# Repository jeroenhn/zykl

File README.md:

# ReZyklus Project

## A clone of the Zyklus MPS-1

The **ReZyklus Project** is an open-source effort to recreate the original **Zyklus MPS-1**.

This repository contains everything required to build your own Zyklus MPS-1 clone, aptly named 'ReZyklus', including hardware design files, panel layouts, and supporting documentation.

See my blog for some more info on the project:
https://www.zyklus-mps.com

There is a Discord server you can join specifically for this project:
https://discord.gg/zFuuCRRDz4

This is also the place where we think and talk about a succesor, the V2 which is mainly carried by David Perbal and will be a system based on the Teensy platform most likely. 

So what is the Zyklus MPS-1? 
A Midi Performance System. It's more than just a sequencer, it's kinda like an 80's version of a launchpad. 
There's really no better way to understand than to have one of the original developers show it to you, so check out Pete Kellocks video demo's of the Zyklus:
https://zyklus-mps.com/videos

Shout out to the team:

Paul McMurray (Technical genius who did most of the actual cloning work)

Marcel Donné (Tester/builder who build one of the first clones)

David Perbal (Another tester/builder who build two of 'm and is carrying the V2 project for the succesor of the ReZyklus - a Teensy based modern implementation)

Panu Talus (Zyklus enthausiast who for years has accumulated all sorts of historical information on the various units. Owner of an original)

And I'm Jeroen (Vangelis gear nut, founder of this project, also owns 2 originals and is restoring Vangelis orignal 'Direct' system).

---

## What’s in this repository

- **Bill of Materials (BOM)**  
  Detailed BOM spreadsheets provide a complete shopping list for the build.

- **PCB & Panel Design Files**  
  All PCB designs and front-panel files are provided.  
  The boards and panels were manufactured using **JLCPCB**, noting that their minimum order quantity is typically **5 units per board or panel**.

- **Case Parts**  
  Some enclosure components are **3D-printed**.  
  The required STL files are included in the repository.

- **Aluminium Dials**  
  Custom aluminium dials were also produced through **JLCPCB**, a working stepfile is included. The Case Parts also contain a file for a 3d printed version. 
  The alu dials need the threads tapped for M4 grub screws. 
  
- **Resource Links**  

  To come: links to various shops for parts, such as the PB86 type switches etc. 

---

## Firmware / OS Status

The original Zyklus operating system is still being worked on. Once ready for publication, it will be added here. The codebase is z80 Assembly and written in a very specific, old assembler which you'll need to compile and link. 

In the meantime, prebuilt EPROM binary files are provided, allowing you to build a fully functional Zyklus clone today while development continues.

---

## Credits & Acknowledgements

### Original Zyklus MPS-1 (1986)

The original Zyklus MPS-1 was created in 1986 by:

- Bill Marshall  
- Pete Kellock  
- Graham Mair  

Bill Marshall and Pete Kellock have generously given their blessing for this clone project to be released as open source.

---

### ReZyklus Project — Primary Contribution

It cannot be overstated that the vast majority of the work on this project has been carried out by Paul McMurray.

This includes, but is not limited to:

- KiCad schematics and PCB layouts  
- Panel designs & lauouts 
- 3D-printed parts  
- Electronics debugging  

Without Paul’s expertise, dedication, and deep understanding of both the original and modern electronics, this project simply would not exist.

Paul McMurray is the MVP of this project and instrumental in helping restoring Direct as well.

---

## Disclaimer

This project is a community-driven, non-commercial recreation intended for educational, historical, and personal use.  
All trademarks and original design concepts remain the property of their respective owners.

## License & Disclaimer

### License

This project is open source and open hardware.

* **Software (firmware, tools, scripts, source code):**
  Licensed under the **GNU General Public License version 3 (GPLv3)** or later.
  You are free to use, modify, and redistribute this software under the terms of the GPL, provided that any distributed modifications remain under the same license.

* **Hardware (schematics, PCB layouts, Gerbers, BOM, and related design files):**
  Licensed under an open hardware copyleft license
  (either **CERN Open Hardware License Version 2 – Strongly Reciprocal (CERN-OHL-S)** *or* **TAPR Open Hardware License**).
  You may use, study, modify, and manufacture hardware based on these designs, provided that any distributed modifications or derivative works are made available under the same license.

The intent of this licensing is to ensure that improvements to this project remain available to the community and cannot be taken proprietary.

THIS PROJECT IS PROVIDED “AS IS”, WITHOUT WARRANTY OF ANY KIND, EXPRESS OR IMPLIED, INCLUDING BUT NOT LIMITED TO MERCHANTABILITY, FITNESS FOR A PARTICULAR PURPOSE, AND NONINFRINGEMENT.

The authors and contributors are not liable for any direct, indirect, incidental, or consequential damages arising from the use, modification, manufacture, or distribution of this hardware or software.

This project is intended for educational, experimental, and research purposes. Use in safety-critical systems (including but not limited to medical devices, life-support systems, or any system where failure could cause injury or death) is expressly discouraged and done entirely at your own risk.

By using, modifying, or manufacturing from this project, you agree that all responsibility for compliance with local laws, regulations, certifications, and safety requirements rests solely with you.

---

### Commercial Use

Commercial use is permitted **only under the terms of the applicable licenses**. Any distributed modifications, derivatives, or products based on this project must remain open and must provide access to corresponding source code and hardware design files under the same license terms.

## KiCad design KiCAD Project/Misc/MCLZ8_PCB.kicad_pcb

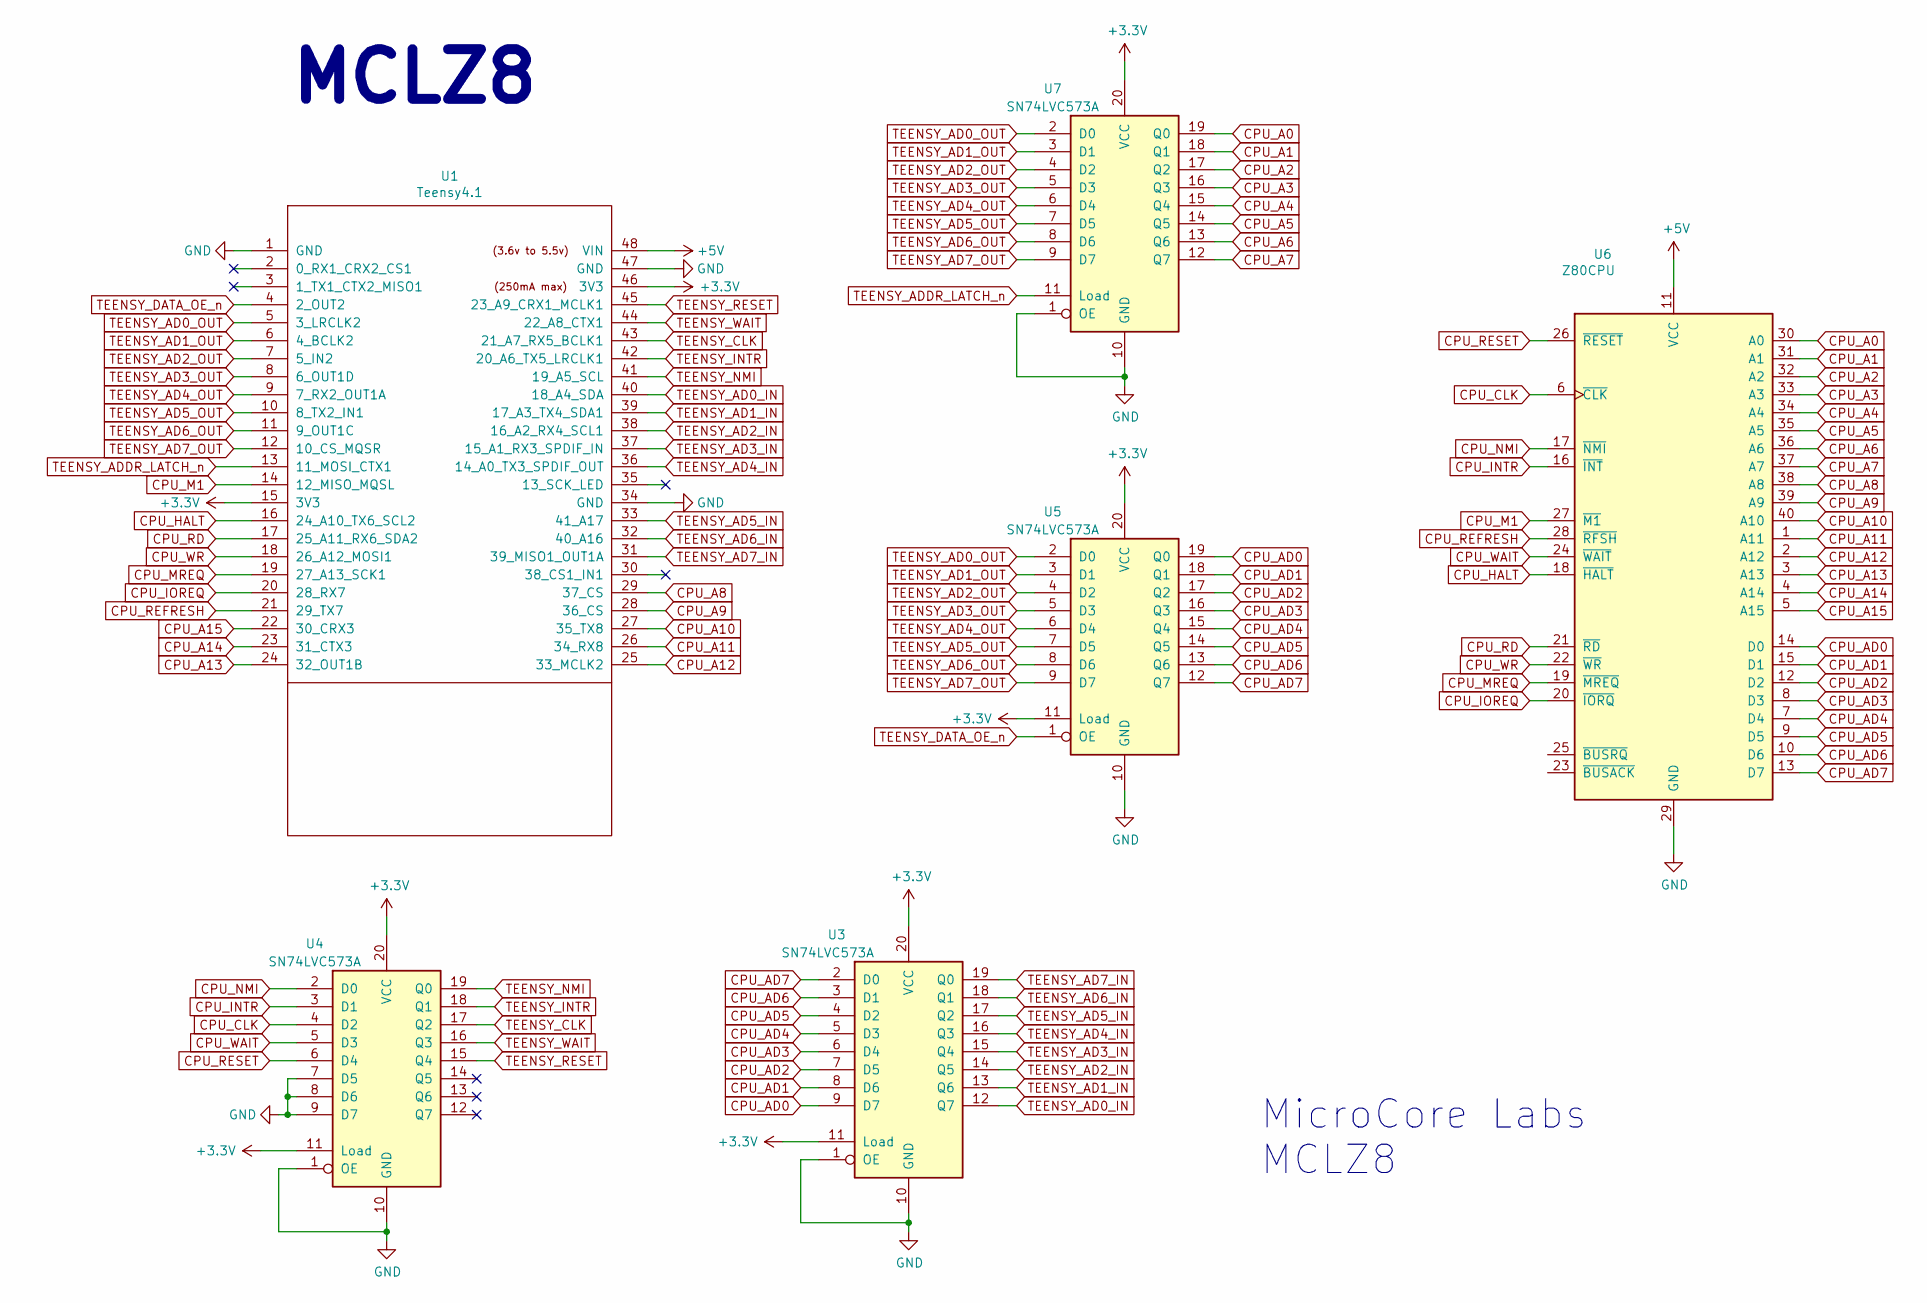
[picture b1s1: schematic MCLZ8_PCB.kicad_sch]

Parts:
U1: Teensy4.1; Teensy41_Ted_Modified
U3, U4, U5, U7: SN74LVC573A; TSSOP-20_4.4x6.5mm_P0.65mm
U6: Z80CPU; DIP-40_W15.24mm

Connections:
+3V3: U1.15 (3V3), U1.46 (3V3), U3.11 (Load), U3.20 (VCC), U4.11 (Load), U4.20 (VCC), U5.11 (Load), U5.20 (VCC), U7.20 (VCC)
+5V: U1.48 (VIN), U6.11 (VCC)
CPU_A0: U6.30 (A0), U7.19 (Q0)
CPU_A1: U6.31 (A1), U7.18 (Q1)
CPU_A2: U6.32 (A2), U7.17 (Q2)
CPU_A3: U6.33 (A3), U7.16 (Q3)
CPU_A4: U6.34 (A4), U7.15 (Q4)
CPU_A5: U6.35 (A5), U7.14 (Q5)
CPU_A6: U6.36 (A6), U7.13 (Q6)
CPU_A7: U6.37 (A7), U7.12 (Q7)
CPU_A8: U1.29 (37_CS), U6.38 (A8)
CPU_A9: U1.28 (36_CS), U6.39 (A9)
CPU_A10: U1.27 (35_TX8), U6.40 (A10)
CPU_A11: U1.26 (34_RX8), U6.1 (A11)
CPU_A12: U1.25 (33_MCLK2), U6.2 (A12)
CPU_A13: U1.24 (32_OUT1B), U6.3 (A13)
CPU_A14: U1.23 (31_CTX3), U6.4 (A14)
CPU_A15: U1.22 (30_CRX3), U6.5 (A15)
CPU_AD0: U3.9 (D7), U5.19 (Q0), U6.14 (D0)
CPU_AD1: U3.8 (D6), U5.18 (Q1), U6.15 (D1)
CPU_AD2: U3.7 (D5), U5.17 (Q2), U6.12 (D2)
CPU_AD3: U3.6 (D4), U5.16 (Q3), U6.8 (D3)
CPU_AD4: U3.5 (D3), U5.15 (Q4), U6.7 (D4)
CPU_AD5: U3.4 (D2), U5.14 (Q5), U6.9 (D5)
CPU_AD6: U3.3 (D1), U5.13 (Q6), U6.10 (D6)
CPU_AD7: U3.2 (D0), U5.12 (Q7), U6.13 (D7)
CPU_CLK: U4.4 (D2), U6.6 (~CLK)
CPU_HALT: U1.16 (24_A10_TX6_SCL2), U6.18 (~HALT)
CPU_INTR: U4.3 (D1), U6.16 (~INT)
CPU_IOREQ: U1.20 (28_RX7), U6.20 (~IORQ)
CPU_M1: U1.14 (12_MISO_MQSL), U6.27 (~M1)
CPU_MREQ: U1.19 (27_A13_SCK1), U6.19 (~MREQ)
CPU_NMI: U4.2 (D0), U6.17 (~NMI)
CPU_RD: U1.17 (25_A11_RX6_SDA2), U6.21 (~RD)
CPU_REFRESH: U1.21 (29_TX7), U6.28 (~RFSH)
CPU_RESET: U4.6 (D4), U6.26 (~RESET)
CPU_WAIT: U4.5 (D3), U6.24 (~WAIT)
CPU_WR: U1.18 (26_A12_MOSI1), U6.22 (~WR)
GND: U1.1 (GND), U1.34 (GND), U1.47 (GND), U3.1 (OE), U3.10 (GND), U4.1 (OE), U4.7 (D5), U4.8 (D6), U4.9 (D7), U4.10 (GND), U5.10 (GND), U6.29 (GND), U7.1 (OE), U7.10 (GND)
TEENSY_AD0_IN: U1.40 (18_A4_SDA), U3.12 (Q7)
TEENSY_AD0_OUT: U1.5 (3_LRCLK2), U5.2 (D0), U7.2 (D0)
TEENSY_AD1_IN: U1.39 (17_A3_TX4_SDA1), U3.13 (Q6)
TEENSY_AD1_OUT: U1.6 (4_BCLK2), U5.3 (D1), U7.3 (D1)
TEENSY_AD2_IN: U1.38 (16_A2_RX4_SCL1), U3.14 (Q5)
TEENSY_AD2_OUT: U1.7 (5_IN2), U5.4 (D2), U7.4 (D2)
TEENSY_AD3_IN: U1.37 (15_A1_RX3_SPDIF_IN), U3.15 (Q4)
TEENSY_AD3_OUT: U1.8 (6_OUT1D), U5.5 (D3), U7.5 (D3)
TEENSY_AD4_IN: U1.36 (14_A0_TX3_SPDIF_OUT), U3.16 (Q3)
TEENSY_AD4_OUT: U1.9 (7_RX2_OUT1A), U5.6 (D4), U7.6 (D4)
TEENSY_AD5_IN: U1.33 (41_A17), U3.17 (Q2)
TEENSY_AD5_OUT: U1.10 (8_TX2_IN1), U5.7 (D5), U7.7 (D5)
TEENSY_AD6_IN: U1.32 (40_A16), U3.18 (Q1)
TEENSY_AD6_OUT: U1.11 (9_OUT1C), U5.8 (D6), U7.8 (D6)
TEENSY_AD7_IN: U1.31 (39_MISO1_OUT1A), U3.19 (Q0)
TEENSY_AD7_OUT: U1.12 (10_CS_MQSR), U5.9 (D7), U7.9 (D7)
TEENSY_ADDR_LATCH_n: U1.13 (11_MOSI_CTX1), U7.11 (Load)
TEENSY_CLK: U1.43 (21_A7_RX5_BCLK1), U4.17 (Q2)
TEENSY_DATA_OE_n: U1.4 (2_OUT2), U5.1 (OE)
TEENSY_INTR: U1.42 (20_A6_TX5_LRCLK1), U4.18 (Q1)
TEENSY_NMI: U1.41 (19_A5_SCL), U4.19 (Q0)
TEENSY_RESET: U1.45 (23_A9_CRX1_MCLK1), U4.15 (Q4)
TEENSY_WAIT: U1.44 (22_A8_CTX1), U4.16 (Q3)

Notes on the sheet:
MicroCore Labs MCLZ8
MCLZ8

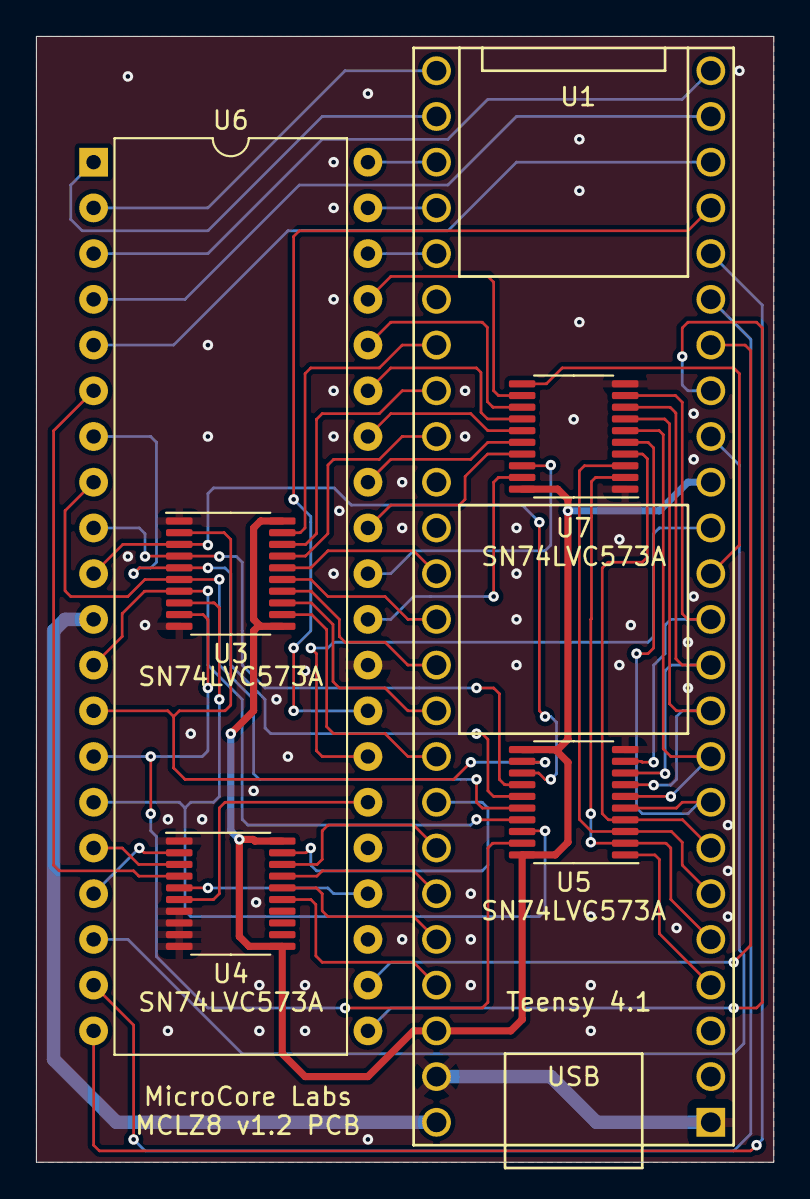
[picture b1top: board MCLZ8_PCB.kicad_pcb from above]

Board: 2 copper layers, 41.0 x 62.5 mm, 6 parts (0 on the bottom side), 62 nets.

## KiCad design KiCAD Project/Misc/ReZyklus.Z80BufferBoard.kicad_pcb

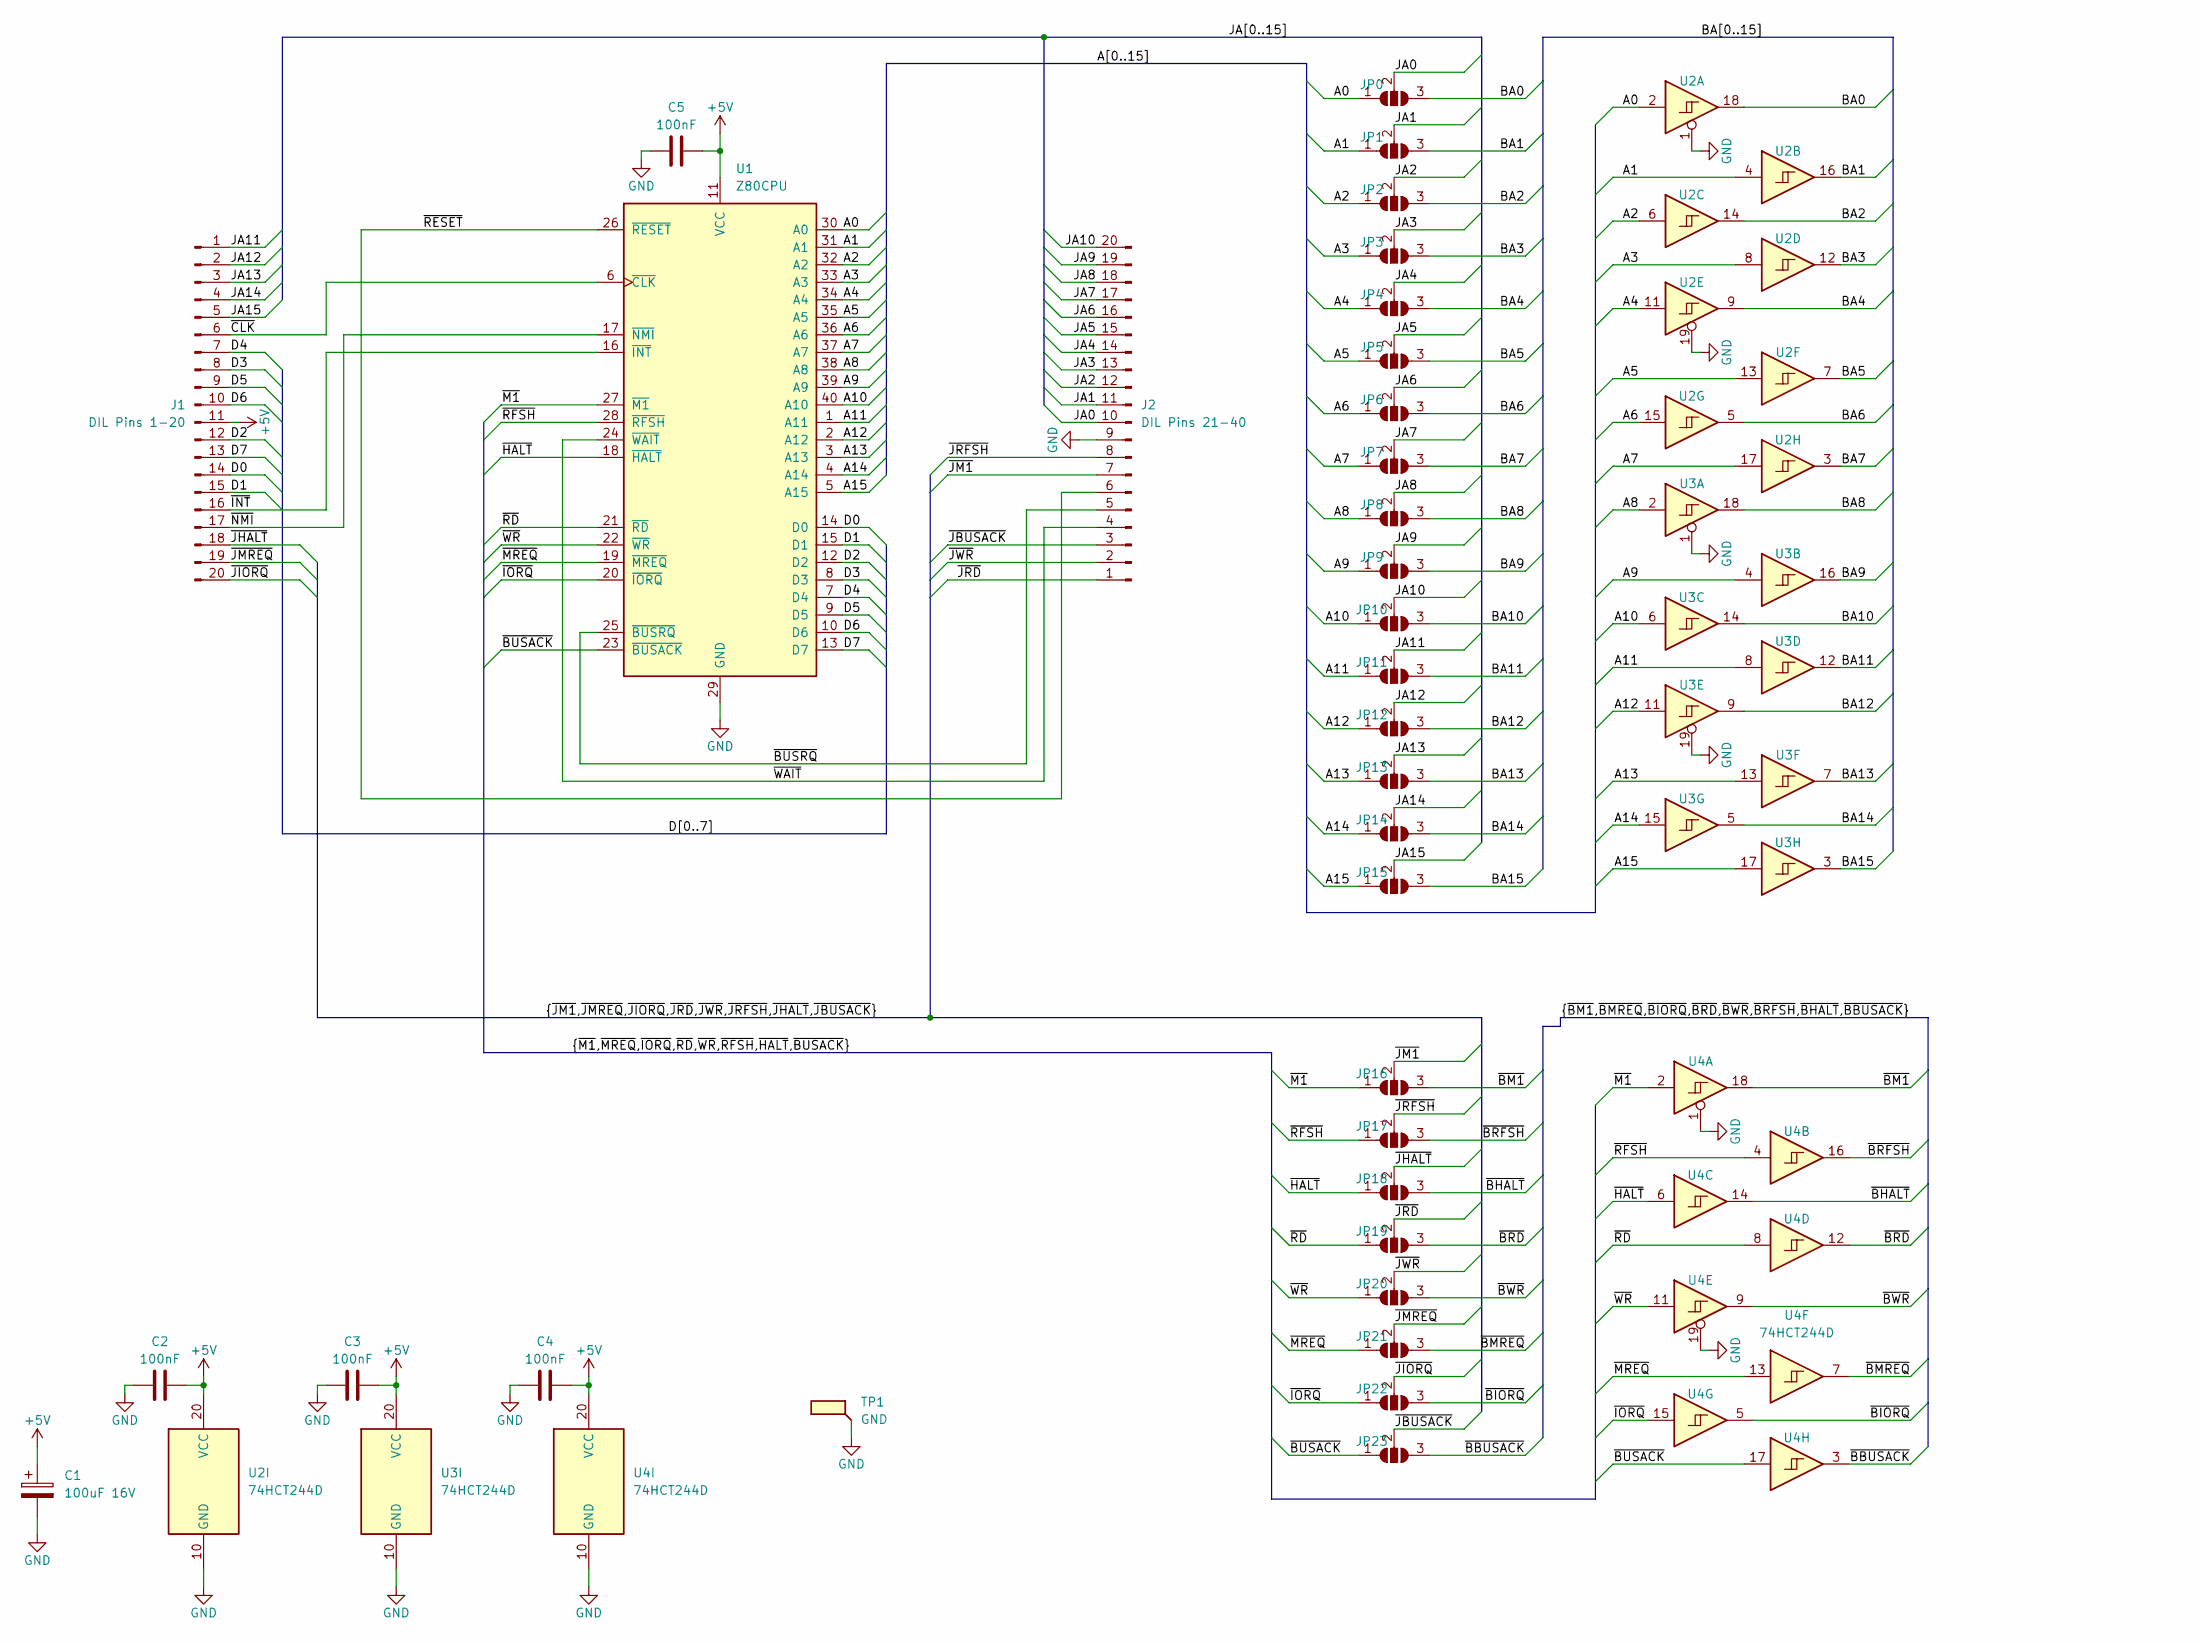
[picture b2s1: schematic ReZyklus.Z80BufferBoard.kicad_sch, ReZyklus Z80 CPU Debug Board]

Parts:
C1: 100uF 16V; CP_Elec_5x5.4
C2, C3, C4, C5: 100nF; C_0805_2012Metric_Pad1.18x1.45mm_HandSolder
J1: DIL Pins 1-20; PinHeader_1x20_P2.54mm_Vertical
J2: DIL Pins 21-40; PinHeader_1x20_P2.54mm_Vertical
JP0: A0; SolderJumper-3_P1.3mm_Open_RoundedPad1.0x1.5mm_NumberLabels
JP1: A1; SolderJumper-3_P1.3mm_Open_RoundedPad1.0x1.5mm_NumberLabels
JP2: A2; SolderJumper-3_P1.3mm_Open_RoundedPad1.0x1.5mm_NumberLabels
JP3: A3; SolderJumper-3_P1.3mm_Open_RoundedPad1.0x1.5mm_NumberLabels
JP4: A4; SolderJumper-3_P1.3mm_Open_RoundedPad1.0x1.5mm_NumberLabels
JP5: A5; SolderJumper-3_P1.3mm_Open_RoundedPad1.0x1.5mm_NumberLabels
JP6: A6; SolderJumper-3_P1.3mm_Open_RoundedPad1.0x1.5mm_NumberLabels
JP7: A7; SolderJumper-3_P1.3mm_Open_RoundedPad1.0x1.5mm_NumberLabels
JP8: A8; SolderJumper-3_P1.3mm_Open_RoundedPad1.0x1.5mm_NumberLabels
JP9: A9; SolderJumper-3_P1.3mm_Open_RoundedPad1.0x1.5mm_NumberLabels
JP10: A10; SolderJumper-3_P1.3mm_Open_RoundedPad1.0x1.5mm_NumberLabels
JP11: A11; SolderJumper-3_P1.3mm_Open_RoundedPad1.0x1.5mm_NumberLabels
JP12: A12; SolderJumper-3_P1.3mm_Open_RoundedPad1.0x1.5mm_NumberLabels
JP13: A13; SolderJumper-3_P1.3mm_Open_RoundedPad1.0x1.5mm_NumberLabels
JP14: A14; SolderJumper-3_P1.3mm_Open_RoundedPad1.0x1.5mm_NumberLabels
JP15: A15; SolderJumper-3_P1.3mm_Open_RoundedPad1.0x1.5mm_NumberLabels
JP16: ~{M1}; SolderJumper-3_P1.3mm_Open_RoundedPad1.0x1.5mm_NumberLabels
JP17: ~{RFSH}; SolderJumper-3_P1.3mm_Open_RoundedPad1.0x1.5mm_NumberLabels
JP18: ~{HALT}; SolderJumper-3_P1.3mm_Open_RoundedPad1.0x1.5mm_NumberLabels
JP19: ~{BRD}; SolderJumper-3_P1.3mm_Open_RoundedPad1.0x1.5mm_NumberLabels
JP20: ~{BWR}; SolderJumper-3_P1.3mm_Open_RoundedPad1.0x1.5mm_NumberLabels
JP21: ~{MREQ}; SolderJumper-3_P1.3mm_Open_RoundedPad1.0x1.5mm_NumberLabels
JP22: ~{IORQ}; SolderJumper-3_P1.3mm_Open_RoundedPad1.0x1.5mm_NumberLabels
JP23: ~{BUSACK}; SolderJumper-3_P1.3mm_Open_RoundedPad1.0x1.5mm_NumberLabels
TP1: GND; TestPoint_THTPad_2.5x2.5mm_Drill1.2mm
U1: Z80CPU; DIP-40_W15.24mm_Socket_LongPads
U2, U3, U4: 74HCT244D; SO-20_12.8x7.5mm_P1.27mm

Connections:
+5V: C1.1, C2.2, C3.2, C4.2, C5.2, J1.11, U1.11 (VCC), U2.20 (VCC), U3.20 (VCC), U4.20 (VCC)
/A0: JP0.1 (A), U1.30 (A0), U2.2
/A1: JP1.1 (A), U1.31 (A1), U2.4
/A2: JP2.1 (A), U1.32 (A2), U2.6
/A3: JP3.1 (A), U1.33 (A3), U2.8
/A4: JP4.1 (A), U1.34 (A4), U2.11
/A5: JP5.1 (A), U1.35 (A5), U2.13
/A6: JP6.1 (A), U1.36 (A6), U2.15
/A7: JP7.1 (A), U1.37 (A7), U2.17
/A8: JP8.1 (A), U1.38 (A8), U3.2
/A9: JP9.1 (A), U1.39 (A9), U3.4
/A10: JP10.1 (A), U1.40 (A10), U3.6
/A11: JP11.1 (A), U1.1 (A11), U3.8
/A12: JP12.1 (A), U1.2 (A12), U3.11
/A13: JP13.1 (A), U1.3 (A13), U3.13
/A14: JP14.1 (A), U1.4 (A14), U3.15
/A15: JP15.1 (A), U1.5 (A15), U3.17
/BA0: JP0.3 (B), U2.18
/BA1: JP1.3 (B), U2.16
/BA2: JP2.3 (B), U2.14
/BA3: JP3.3 (B), U2.12
/BA4: JP4.3 (B), U2.9
/BA5: JP5.3 (B), U2.7
/BA6: JP6.3 (B), U2.5
/BA7: JP7.3 (B), U2.3
/BA8: JP8.3 (B), U3.18
/BA9: JP9.3 (B), U3.16
/BA10: JP10.3 (B), U3.14
/BA11: JP11.3 (B), U3.12
/BA12: JP12.3 (B), U3.9
/BA13: JP13.3 (B), U3.7
/BA14: JP14.3 (B), U3.5
/BA15: JP15.3 (B), U3.3
/D0: J1.14, U1.14 (D0)
/D1: J1.15, U1.15 (D1)
/D2: J1.12, U1.12 (D2)
/D3: J1.8, U1.8 (D3)
/D4: J1.7, U1.7 (D4)
/D5: J1.9, U1.9 (D5)
/D6: J1.10, U1.10 (D6)
/D7: J1.13, U1.13 (D7)
/JA0: J2.10, JP0.2 (C)
/JA1: J2.11, JP1.2 (C)
/JA2: J2.12, JP2.2 (C)
/JA3: J2.13, JP3.2 (C)
/JA4: J2.14, JP4.2 (C)
/JA5: J2.15, JP5.2 (C)
/JA6: J2.16, JP6.2 (C)
/JA7: J2.17, JP7.2 (C)
/JA8: J2.18, JP8.2 (C)
/JA9: J2.19, JP9.2 (C)
/JA10: J2.20, JP10.2 (C)
/JA11: J1.1, JP11.2 (C)
/JA12: J1.2, JP12.2 (C)
/JA13: J1.3, JP13.2 (C)
/JA14: J1.4, JP14.2 (C)
/JA15: J1.5, JP15.2 (C)
/~BBUSACK: JP23.3 (B), U4.3
/~BHALT: JP18.3 (B), U4.14
/~BIORQ: JP22.3 (B), U4.5
/~BM1: JP16.3 (B), U4.18
/~BMREQ: JP21.3 (B), U4.7
/~BRD: JP19.3 (B), U4.12
/~BRFSH: JP17.3 (B), U4.16
/~BUSACK: JP23.1 (A), U1.23 (~BUSACK), U4.17
/~BUSRQ: J2.5, U1.25 (~BUSRQ)
/~BWR: JP20.3 (B), U4.9
/~CLK: J1.6, U1.6 (~CLK)
/~HALT: JP18.1 (A), U1.18 (~HALT), U4.6
/~INT: J1.16, U1.16 (~INT)
/~IORQ: JP22.1 (A), U1.20 (~IORQ), U4.15
/~JBUSACK: J2.3, JP23.2 (C)
/~JHALT: J1.18, JP18.2 (C)
/~JIORQ: J1.20, JP22.2 (C)
/~JM1: J2.7, JP16.2 (C)
/~JMREQ: J1.19, JP21.2 (C)
/~JRD: J2.1, JP19.2 (C)
/~JRFSH: J2.8, JP17.2 (C)
/~JWR: J2.2, JP20.2 (C)
/~M1: JP16.1 (A), U1.27 (~M1), U4.2
/~MREQ: JP21.1 (A), U1.19 (~MREQ), U4.13
/~NMI: J1.17, U1.17 (~NMI)
/~RD: JP19.1 (A), U1.21 (~RD), U4.8
/~RESET: J2.6, U1.26 (~RESET)
/~RFSH: JP17.1 (A), U1.28 (~RFSH), U4.4
/~WAIT: J2.4, U1.24 (~WAIT)
/~WR: JP20.1 (A), U1.22 (~WR), U4.11
GND: C1.2, C2.1, C3.1, C4.1, C5.1, J2.9, TP1.1, U1.29 (GND), U2.1, U2.10 (GND), U2.19, U3.1, U3.10 (GND), U3.19, U4.1, U4.10 (GND), U4.19

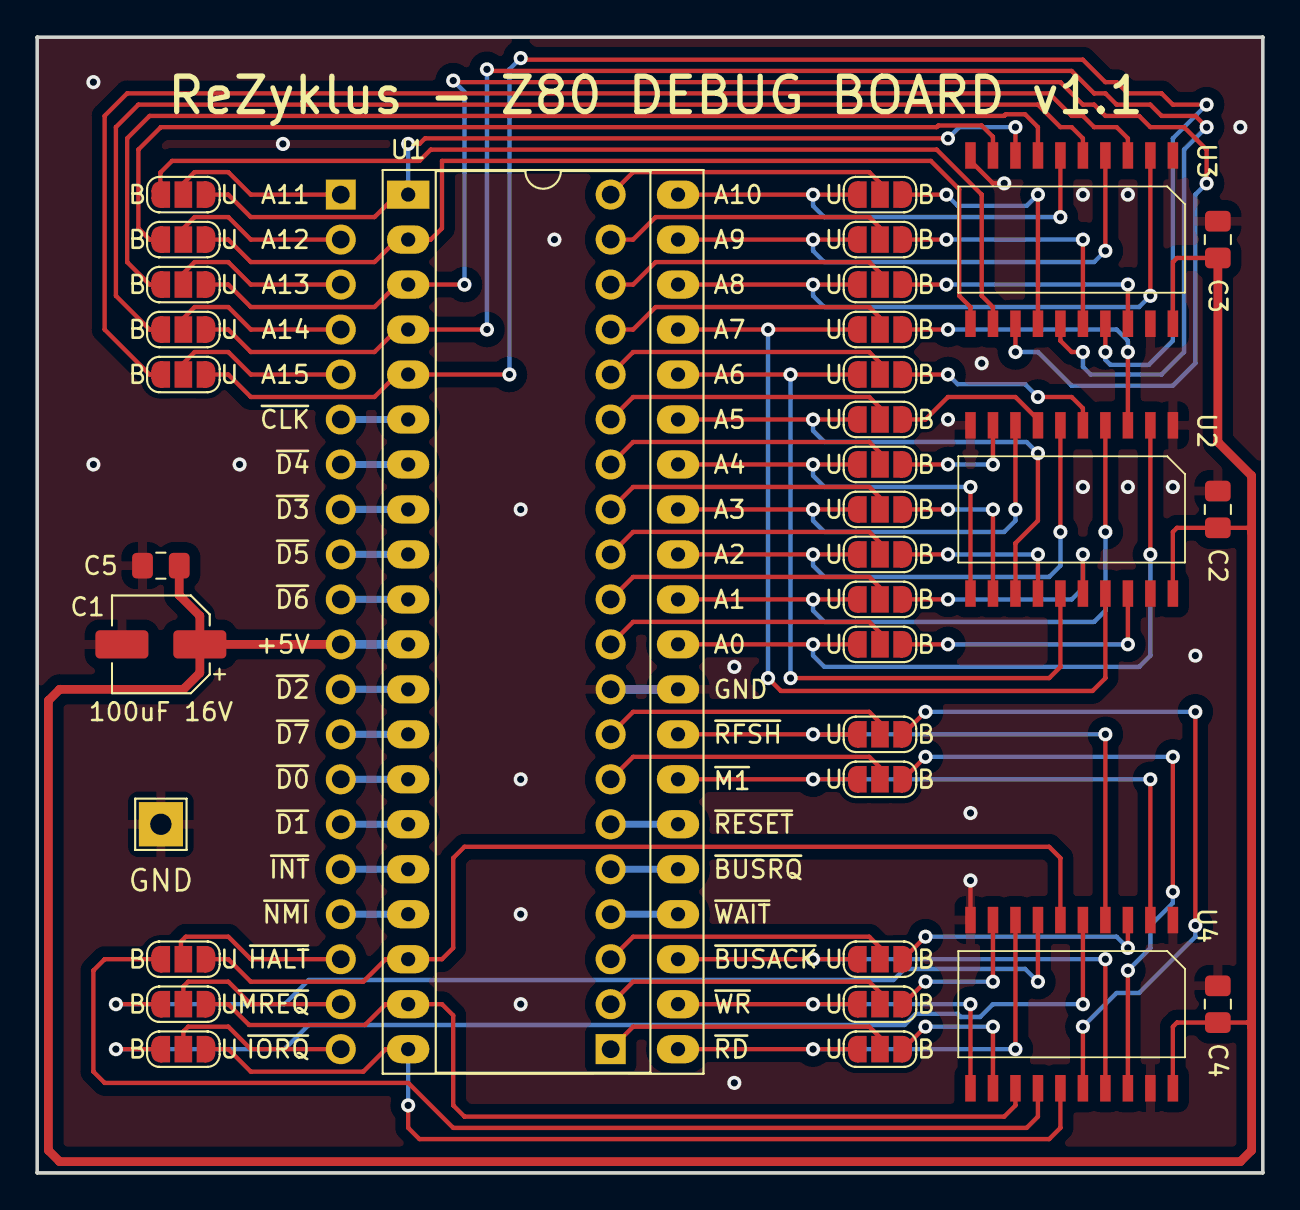
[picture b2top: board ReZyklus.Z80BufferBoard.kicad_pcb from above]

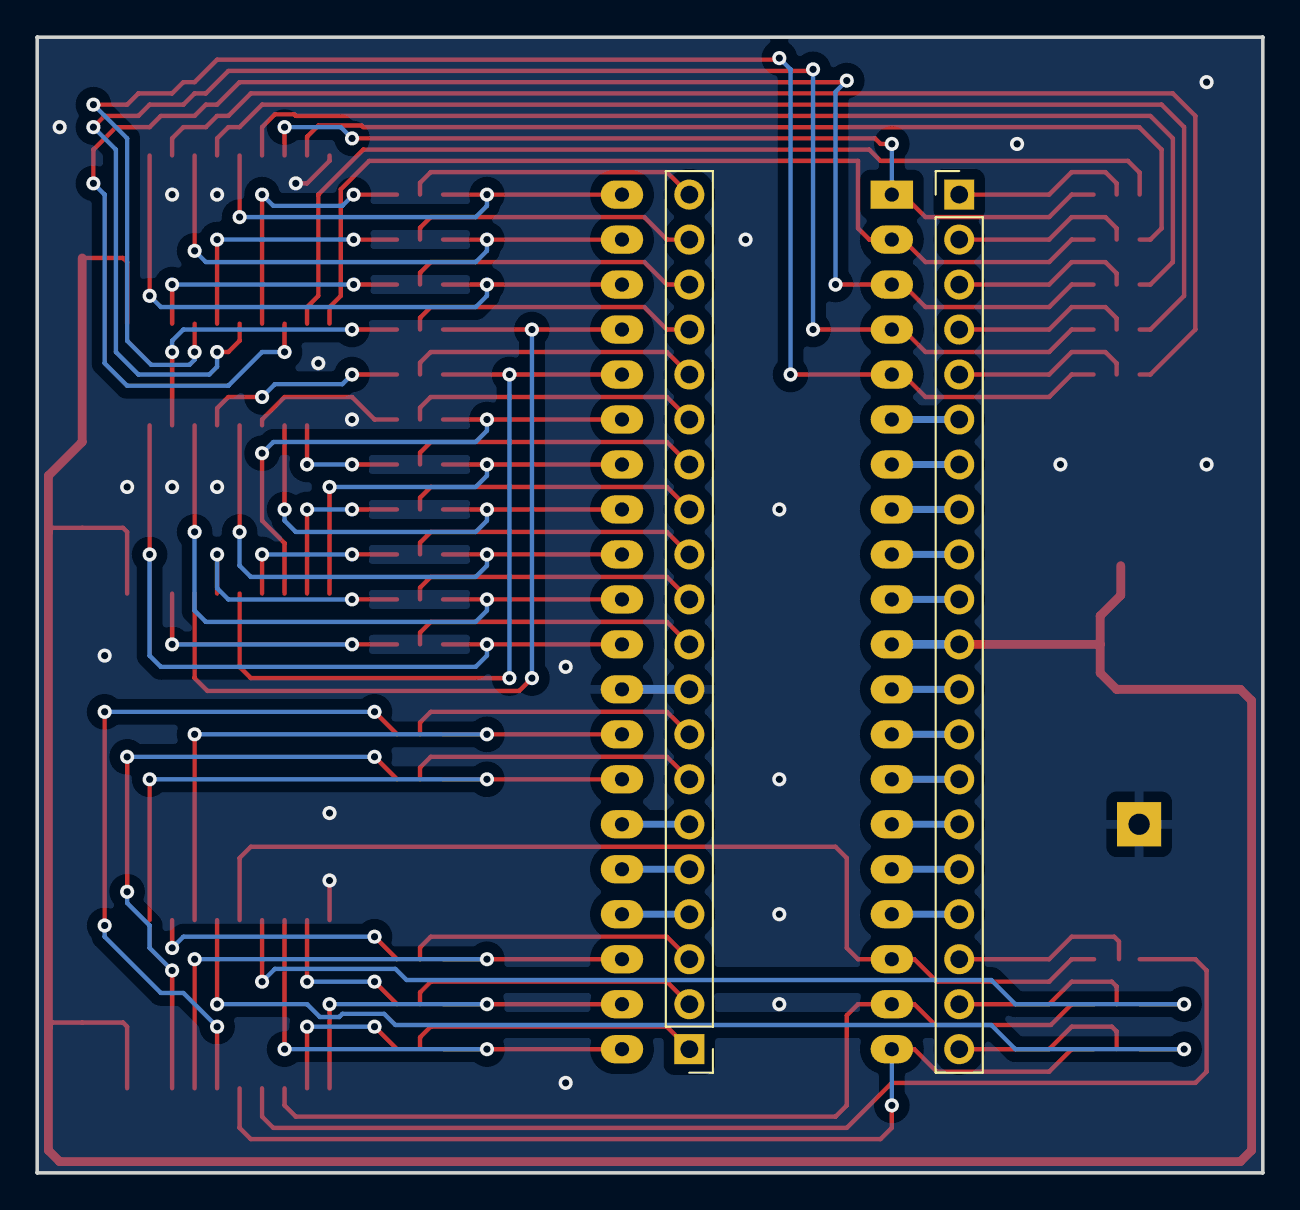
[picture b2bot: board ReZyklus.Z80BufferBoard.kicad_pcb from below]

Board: 2 copper layers, 69.2 x 64.1 mm, 36 parts (2 on the bottom side), 88 nets.

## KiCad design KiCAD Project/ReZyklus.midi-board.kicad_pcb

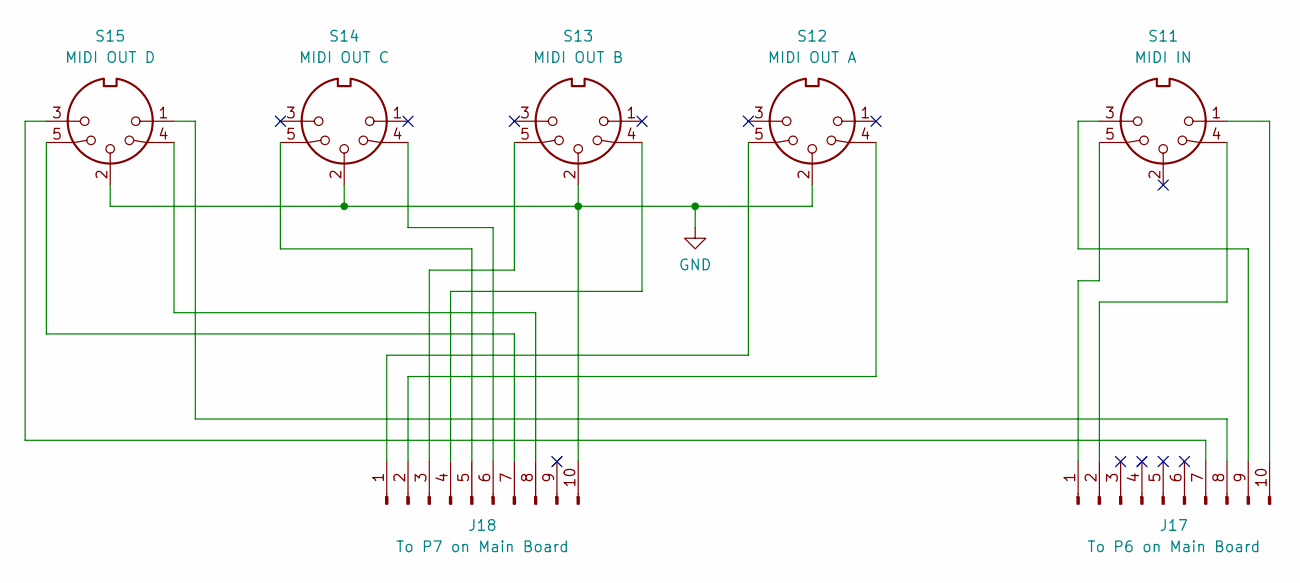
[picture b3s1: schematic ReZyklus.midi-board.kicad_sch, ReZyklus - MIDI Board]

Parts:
J17: To P6 on Main Board; Molex_KK-254_AE-6410-10A_1x10_P2.54mm_Vertical
J18: To P7 on Main Board; Molex_KK-254_AE-6410-10A_1x10_P2.54mm_Vertical
S11: MIDI IN; 5-Pin DIN Wired
S12: MIDI OUT A; 5-Pin DIN Wired
S13: MIDI OUT B; 5-Pin DIN Wired
S14: MIDI OUT C; 5-Pin DIN Wired
S15: MIDI OUT D; 5-Pin DIN Wired

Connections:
GND: J18.10, S12.2, S13.2, S14.2, S15.2
unnamed: J17.1, S11.5
unnamed: J17.2, S11.4
unnamed: J17.7, S15.3
unnamed: J17.8, S15.1
unnamed: J17.9, S11.3
unnamed: J17.10, S11.1
unnamed: J18.1, S12.5
unnamed: J18.2, S12.4
unnamed: J18.3, S13.5
unnamed: J18.4, S13.4
unnamed: J18.5, S14.5
unnamed: J18.6, S14.4
unnamed: J18.7, S15.5
unnamed: J18.8, S15.4

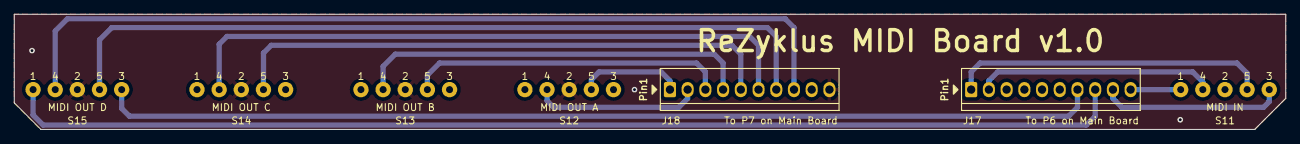
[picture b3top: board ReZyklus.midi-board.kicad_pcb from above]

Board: 2 copper layers, 182.2 x 16.5 mm, 7 parts (0 on the bottom side), 15 nets.

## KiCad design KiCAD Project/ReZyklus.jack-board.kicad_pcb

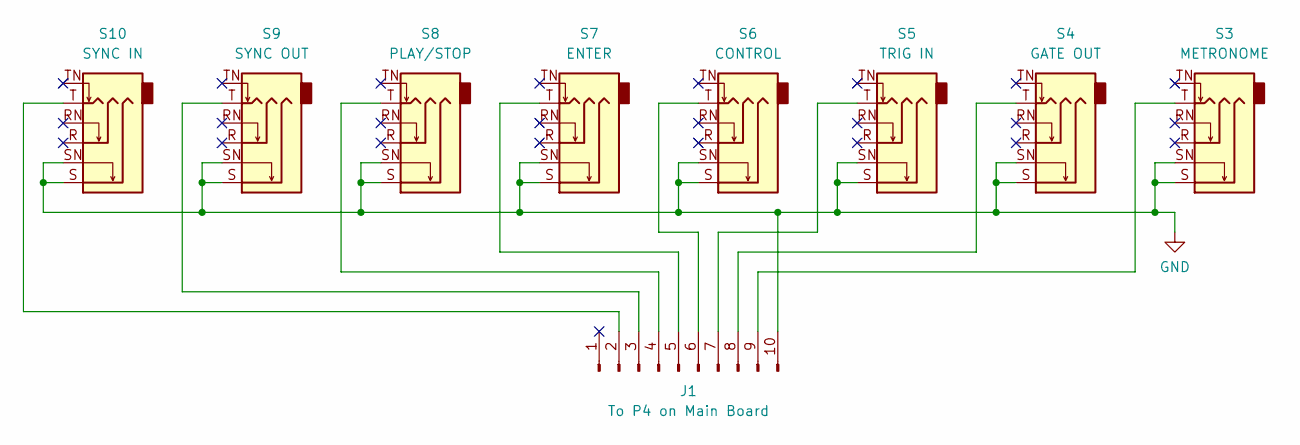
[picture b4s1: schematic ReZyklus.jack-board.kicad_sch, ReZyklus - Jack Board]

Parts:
J1: To P4 on Main Board; Molex_KK-254_AE-6410-10A_1x10_P2.54mm_Vertical
S3: METRONOME; Jack_6.35mm_Neutrik_NMJ6HFD2_Horizontal
S4: GATE OUT; Jack_6.35mm_Neutrik_NMJ6HFD2_Horizontal
S5: TRIG IN; Jack_6.35mm_Neutrik_NMJ6HFD2_Horizontal
S6: CONTROL; Jack_6.35mm_Neutrik_NMJ6HFD2_Horizontal
S7: ENTER; Jack_6.35mm_Neutrik_NMJ6HFD2_Horizontal
S8: PLAY/STOP; Jack_6.35mm_Neutrik_NMJ6HFD2_Horizontal
S9: SYNC OUT; Jack_6.35mm_Neutrik_NMJ6HFD2_Horizontal
S10: SYNC IN; Jack_6.35mm_Neutrik_NMJ6HFD2_Horizontal

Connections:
GND: J1.10, S3.S, S3.SN, S4.S, S4.SN, S5.S, S5.SN, S6.S, S6.SN, S7.S, S7.SN, S8.S, S8.SN, S9.S, S9.SN, S10.S, S10.SN
unnamed: J1.2, S10.T
unnamed: J1.3, S9.T
unnamed: J1.4, S8.T
unnamed: J1.5, S7.T
unnamed: J1.6, S6.T
unnamed: J1.7, S5.T
unnamed: J1.8, S4.T
unnamed: J1.9, S3.T

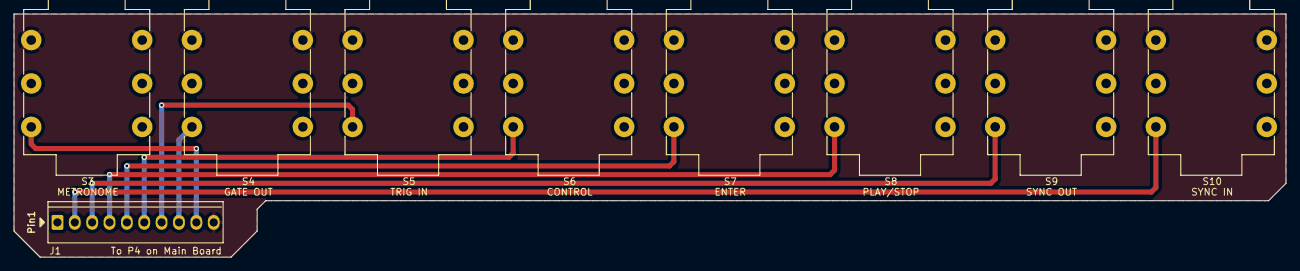
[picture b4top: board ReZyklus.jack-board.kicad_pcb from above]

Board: 2 copper layers, 186.1 x 35.6 mm, 9 parts (0 on the bottom side), 9 nets.
